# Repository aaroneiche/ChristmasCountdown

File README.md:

# Christmas Countdown

Christmas Countdown is a Christmas Ornament that counts down to Christmas day (or really any day) in Binary. Using two rows of LEDs, it displays the Days & Hours and then the Minutes & seconds remaining until Christmas Day. If you want to learn about how I approached developing it, and how many times I got it wrong, you can read my writeup of [the whole adventure here](https://aaroneiche.com/2023/02/05/christmas-countdown/) 

The heart of the circuit is an ESP32-C3-Mini-1. It drives fourteen SK6812 LEDs that display the time, as well as an indicator of the current mode. The time is kept by a PCF85363 with a battery backup . The ornament runs off of 5v, and requires about 1A with the LEDs running at full brightness (I do not recommend this, these LEDs will melt your face off) 

### Setting the time.

To set the ornament, press and hold the left button for 3 seconds and release. On the bottom row it shows what you're setting (year, month, day, hour, minute, second) and the top row displays the current value. There are 12 settings in all, 6 for the current date/time, and 6 for the target date/time. You can advance to the next value to set by pressing the left button. You can increase the value by pressing the right button. The value will return to zero (or one) after the maximum value has been reached. You do not need to do any math about timing, just set the current and target dates/times. The default target date is December 25th, 00:00:00 AM. You may wish to set the time to December 25th, 08:00:00 for when you start Christmas with your family. Perhaps you observe Orthodox Christmas and want to set it for January 7th.

When setting the current date/time, the whole bottom row will be lit with the value you're setting flashing on and off.
Here is an example of setting the current year (22 - for 2022)

When setting the target date/time, the whole bottom row will be off with the value you're setting flashing on an off.
Here is an example of setting the target month (12 - for December)

When you've finished setting the values, press and hold the right button for 3 seconds. The countdown values will appear.

## Clock battery

If power is lost to Christmas Countdown, the RTC will go into battery mode automatically and will continue to count time. The RTC battery runs on very low power mode consuming ~320nA. 

If the battery is removed, some settings will be maintained on Christmas Countdown. The current time will need to be set again.

## Adding to the the software

I wrote most of this software in VSCode with PlatformIO. I programmed the Esp32-C3 using a CP1202 USB->UART adapter, and connecting the DTR and RTS pins. Alternatively, you should be able to put the board in download mode by holding down the "Program" button on the back while pressing and releasing the "Reset" button.

Changes to the firmware should be pretty easy to make. It's all (in)conveniently in a single file. A couple of helpful hints: 

A clock interrupt fires 1024 times a second. This is how the clock, and the various display updates are handled. There are currently events that execute at 1s, 0.5s and 0.25s. Any handler can be added to the `quarterSecondOverflow`, `halfSecondOverflow`, and `secondOverflow` branches in the loop. These are good locations for executing frequent.

The very last execution in the loop is to update the display. This creates a buffer and that is fed to the `displayFromBuffer` method. This should make it easy to set the display to whatever you want. To prevent your LEDs from getting overwritten by other stuff, make sure to pay attention to the other modes that are writing to the display. The easiest way to avoid this is to make your own Display Mode - you can add one about line 50 in the `enum DisplayMode`.

# Hardware

I typically order PCBs with 1oz copper, HASL Lead-Free. The Color isn't super important. I think that Black looks best, and if you're willing to splurge, Gold ENIG looks very nice on the Snowflake on the front.

The Piezo buzzer does not currently do anything. I have run some tests where I can get it to play some simple music. It definitely works, I just haven't done anything with it yet.

Taking advantage of the Interact HTML BOM, there's a component placement page included in this repo (`ibom.html`)

## What about Wifi?!?!

Yes, the onboard chip has support for Wifi. Which means that you could set the time automatically using NTP. And you could change settings on a webpage even! I have written some code to support these features, and when they're polished I will be making them available. For now, Christmas countdown must be programmed using a couple of buttons and your cunning.

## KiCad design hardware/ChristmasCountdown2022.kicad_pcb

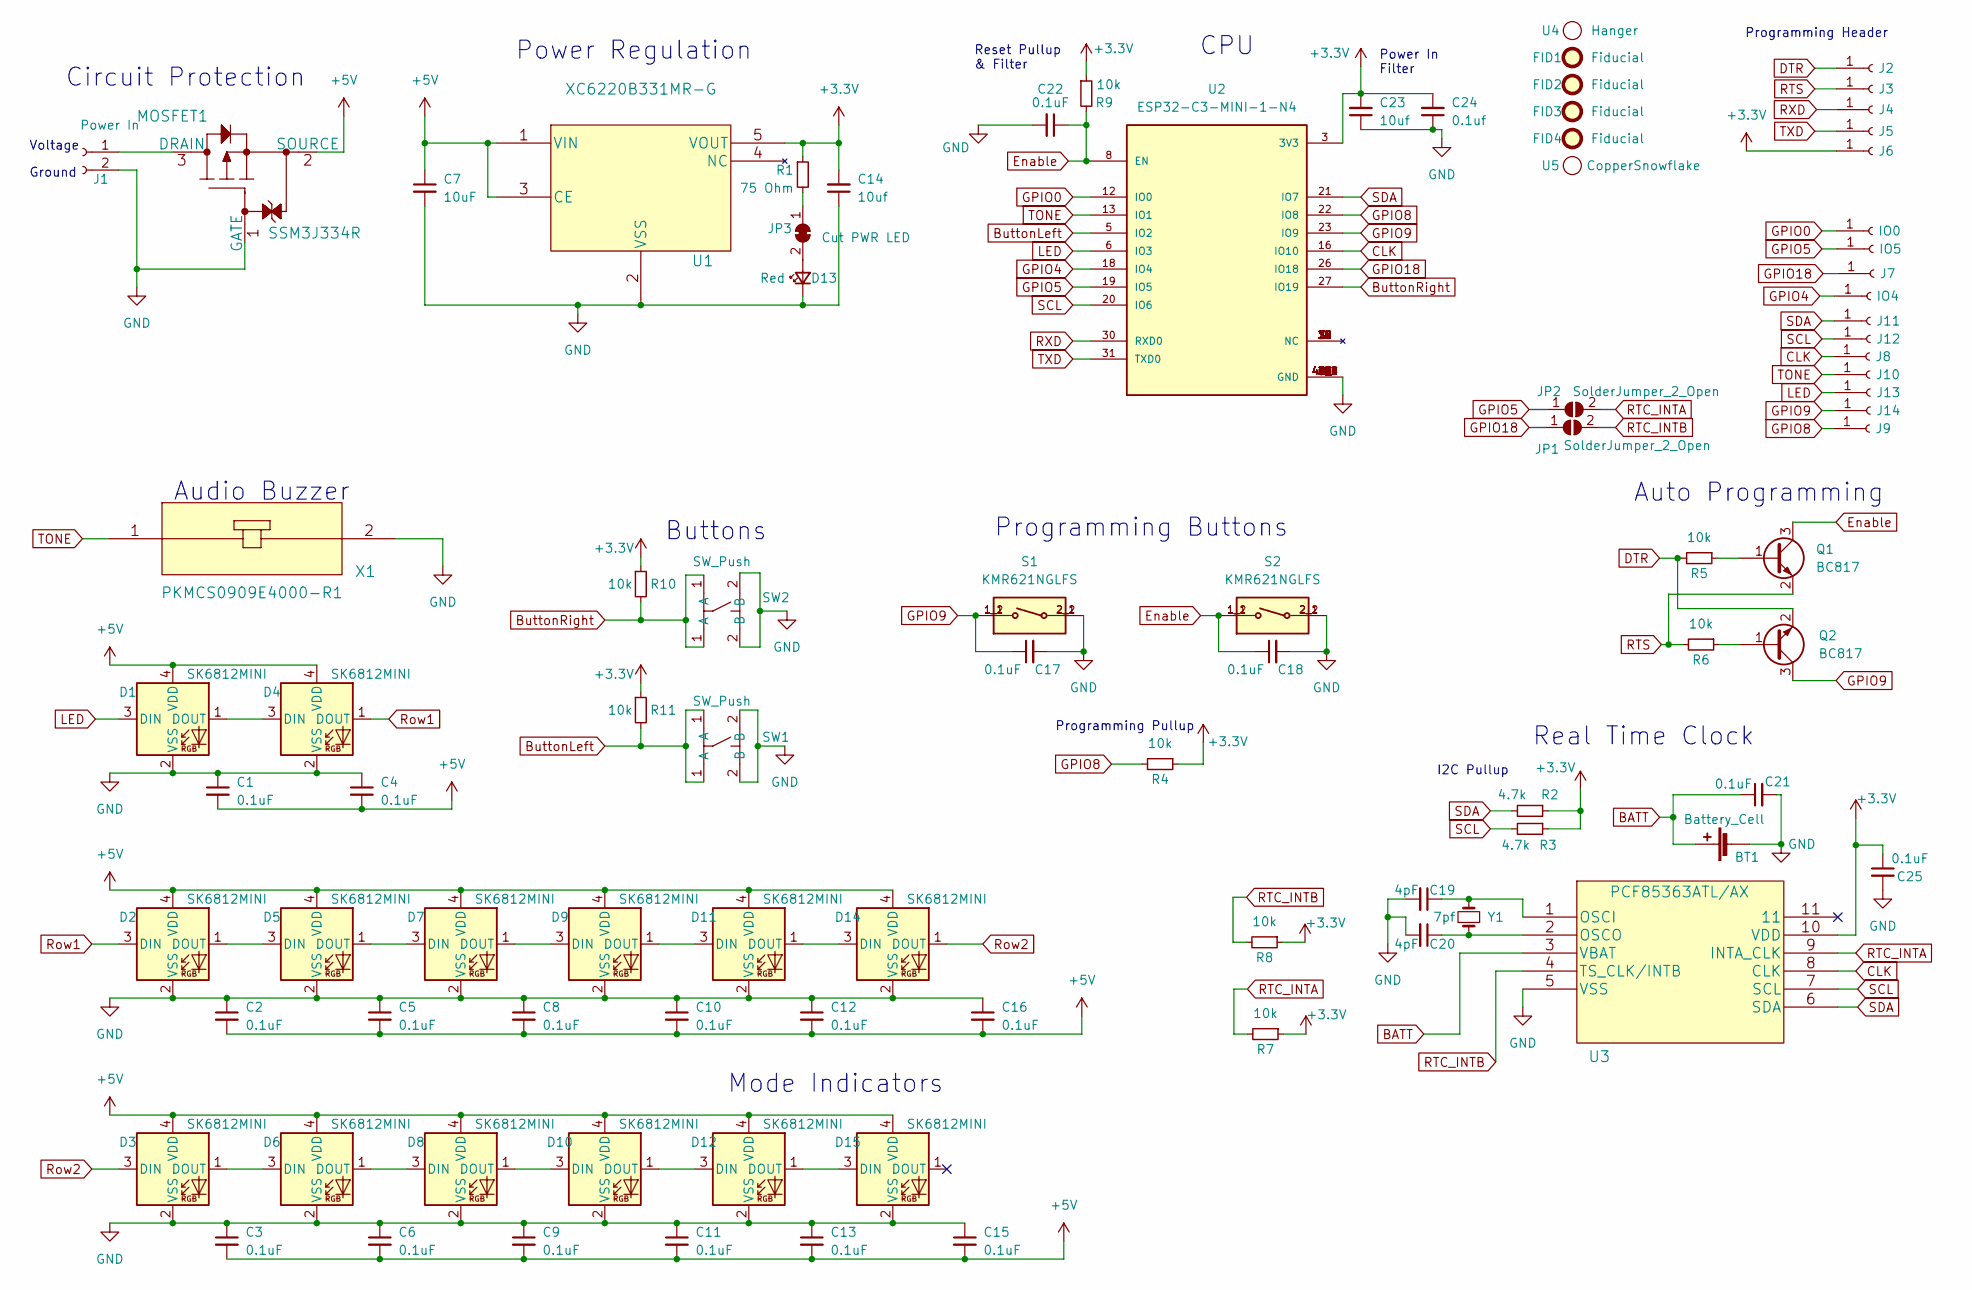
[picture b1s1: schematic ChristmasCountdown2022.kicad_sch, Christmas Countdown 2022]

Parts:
BT1: Battery_Cell; BatteryHolder_LINX_BAT-HLD-012-SMT
C1, C2, C3, C4, C5, C6, C8, C9, C10, C11, C12, C13, C15, C16, C17, C18, C21, C22, C25: 0.1uF; C_0805_2012Metric
C7: 10uF; C_0805_2012Metric
C14, C23: 10uf; C_0805_2012Metric
C19, C20: 4pF; R_0805_2012Metric
C24: 0.1uf; C_0805_2012Metric
D1, D2, D3, D4, D5, D6, D7, D8, D9, D10, D11, D12, D14, D15: SK6812MINI; LED_SK6812MINI_PLCC4_3.5x3.5mm_P1.75mm
D13: Red; LED_0805_2012Metric
FID1, FID2, FID3, FID4: Fiducial; Fiducial_0.5mm_Mask1mm
IO0: IO0; TestPoint_Pad_D2.0mm
IO4: IO4; TestPoint_Pad_D2.0mm
IO5: IO5; TestPoint_Pad_D2.0mm
J1: Power In; Hand_solderable_1x2
J2, J3, J4, J5, J6: Conn_01x01_Female; PinSocket_1x01_P2.54mm_Vertical
J7: IO18; TestPoint_Pad_D2.0mm
J8: CLK; PinSocket_1x01_P2.54mm_Vertical
J9: IO8; TestPoint_Pad_D2.0mm
J10: TONE; PinSocket_1x01_P2.54mm_Vertical
J11: SDA; TestPoint_Pad_D2.0mm
J12: SCL; TestPoint_Pad_D2.0mm
J13: LED; PinSocket_1x01_P2.54mm_Vertical
J14: IO9; TestPoint_Pad_D2.0mm
JP1, JP2: SolderJumper_2_Open; SolderJumper-2_P1.3mm_Open_RoundedPad1.0x1.5mm
JP3: Cut PWR LED; SolderJumper-2_P1.3mm_Bridged_RoundedPad1.0x1.5mm
MOSFET1: SSM3J334R
Q1, Q2: BC817; SOT-23
R1: 75 Ohm; R_0805_2012Metric
R2, R3: 4.7k; R_0805_2012Metric
R4, R5, R6, R7, R8, R9, R10, R11: 10k; R_0805_2012Metric
S1, S2: KMR621NGLFS; SW_KMR621NGLFS; PARTREV N/A
SW1, SW2: SW_Push; EVQQ2B03W; MFG_Part_number EVQ-Q2F02W
U1: XC6220B331MR-G
U2: ESP32-C3-MINI-1-N4; XCVR_ESP32-C3-MINI-1-N4; PARTREV v1.0
U3: PCF85363ATL/AX; PCF85363ATL_AX
U4: Hanger
U5: CopperSnowflake; CopperSnowflakeGraphic
X1: PKMCS0909E4000-R1
Y1: 7pf; CM8V-T1A-Crystal

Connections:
+3.3V: C14.2, C23.2, C24.2, C25.1, J6.1, R1.1, R2.1, R3.1, R4.1, R7.1, R8.1, R9.1, R10.1, R11.1, U1.5 (VOUT), U2.3 (3V3), U3.10 (VDD)
+5V: C1.2, C2.2, C3.2, C4.2, C5.2, C6.2, C7.1, C8.2, C9.2, C10.2, C11.2, C12.2, C13.2, C15.2, C16.2, D1.4 (VDD), D2.4 (VDD), D3.4 (VDD), D4.4 (VDD), D5.4 (VDD), D6.4 (VDD), D7.4 (VDD), D8.4 (VDD), D9.4 (VDD), D10.4 (VDD), D11.4 (VDD), D12.4 (VDD), D14.4 (VDD), D15.4 (VDD), MOSFET1.2 (SOURCE), U1.1 (VIN), U1.3 (CE)
BATT: BT1.1 (+), C21.1, U3.3 (VBAT)
ButtonLeft: R11.2, SW1.1 (A), U2.5 (IO2)
ButtonRight: R10.2, SW2.1 (A), U2.27 (IO19)
CLK: J8.1, U2.16 (IO10), U3.8 (CLK)
DTR: J2.1, Q2.2 (E), R5.2
Enable: C18.1, C22.1, Q1.3 (C), R9.2, S2.1_1, S2.1_2, U2.8 (EN)
GND: BT1.2 (-), C1.1, C2.1, C3.1, C4.1, C5.1, C6.1, C7.2, C8.1, C9.1, C10.1, C11.1, C12.1, C13.1, C14.1, C15.1, C16.1, C17.2, C18.2, C19.2, C20.2, C21.2, C22.2, C23.1, C24.1, C25.2, D1.2 (VSS), D2.2 (VSS), D3.2 (VSS), D4.2 (VSS), D5.2 (VSS), D6.2 (VSS), D7.2 (VSS), D8.2 (VSS), D9.2 (VSS), D10.2 (VSS), D11.2 (VSS), D12.2 (VSS), D13.1 (K), D14.2 (VSS), D15.2 (VSS), J1.2, MOSFET1.1 (GATE), S1.2_1, S1.2_2, S2.2_1, S2.2_2, SW1.2 (B), SW2.2 (B), U1.2 (VSS), U2.1 (GND), U2.2 (GND), U2.11 (GND), U2.14 (GND), U2.36 (GND), U2.37 (GND), U2.38 (GND), U2.39 (GND), U2.40 (GND), U2.41 (GND), U2.42 (GND), U2.43 (GND), U2.44 (GND), U2.45 (GND), U2.46 (GND), U2.47 (GND), U2.48 (GND), U2.49_1 (GND), U2.49_2 (GND), U2.49_3 (GND), U2.49_4 (GND), U2.49_5 (GND), U2.49_6 (GND), U2.49_7 (GND), U2.49_8 (GND), U2.49_9 (GND), U2.50 (GND), U2.51 (GND), U2.52 (GND), U2.53 (GND), U3.5 (VSS), X1.2
GPIO0: IO0.1, U2.12 (IO0)
GPIO4: IO4.1, U2.18 (IO4)
GPIO5: IO5.1, JP2.1 (A), U2.19 (IO5)
GPIO8: J9.1, R4.2, U2.22 (IO8)
GPIO9: C17.1, J14.1, Q2.3 (C), S1.1_1, S1.1_2, U2.23 (IO9)
GPIO18: J7.1, JP1.1 (A), U2.26 (IO18)
LED: D1.3 (DIN), J13.1, U2.6 (IO3)
unnamed: C19.1, U3.1 (OSCI), Y1.2
unnamed: C20.1, U3.2 (OSCO), Y1.1
unnamed: D1.1 (DOUT), D4.3 (DIN)
unnamed: D2.1 (DOUT), D5.3 (DIN)
unnamed: D3.1 (DOUT), D6.3 (DIN)
unnamed: D5.1 (DOUT), D7.3 (DIN)
unnamed: D6.1 (DOUT), D8.3 (DIN)
unnamed: D7.1 (DOUT), D9.3 (DIN)
unnamed: D10.1 (DOUT), D12.3 (DIN)
unnamed: D8.1 (DOUT), D10.3 (DIN)
unnamed: D11.1 (DOUT), D14.3 (DIN)
unnamed: D9.1 (DOUT), D11.3 (DIN)
unnamed: D12.1 (DOUT), D15.3 (DIN)
unnamed: D13.2 (A), JP3.2 (B)
unnamed: J1.1, MOSFET1.3 (DRAIN)
unnamed: JP3.1 (A), R1.2
unnamed: Q1.1 (B), R5.1
unnamed: Q2.1 (B), R6.1
RTC_INTA: JP2.2 (B), R7.2, U3.9 (INTA_CLK)
RTC_INTB: JP1.2 (B), R8.2, U3.4 (TS_CLK/INTB)
RTS: J3.1, Q1.2 (E), R6.2
RXD: J4.1, U2.30 (RXD0)
Row1: D2.3 (DIN), D4.1 (DOUT)
Row2: D3.3 (DIN), D14.1 (DOUT)
SCL: J12.1, R3.2, U2.20 (IO6), U3.7 (SCL)
SDA: J11.1, R2.2, U2.21 (IO7), U3.6 (SDA)
TONE: J10.1, U2.13 (IO1), X1.1
TXD: J5.1, U2.31 (TXD0)

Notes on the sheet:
Auto Programming
Circuit Protection
Power Regulation
CPU
Programming Header
Real Time Clock
Programming Pullup
Mode Indicators
Audio Buzzer
I2C Pullup
Buttons
Voltage
Power In Filter
Ground
Programming Buttons
Reset Pullup & Filter

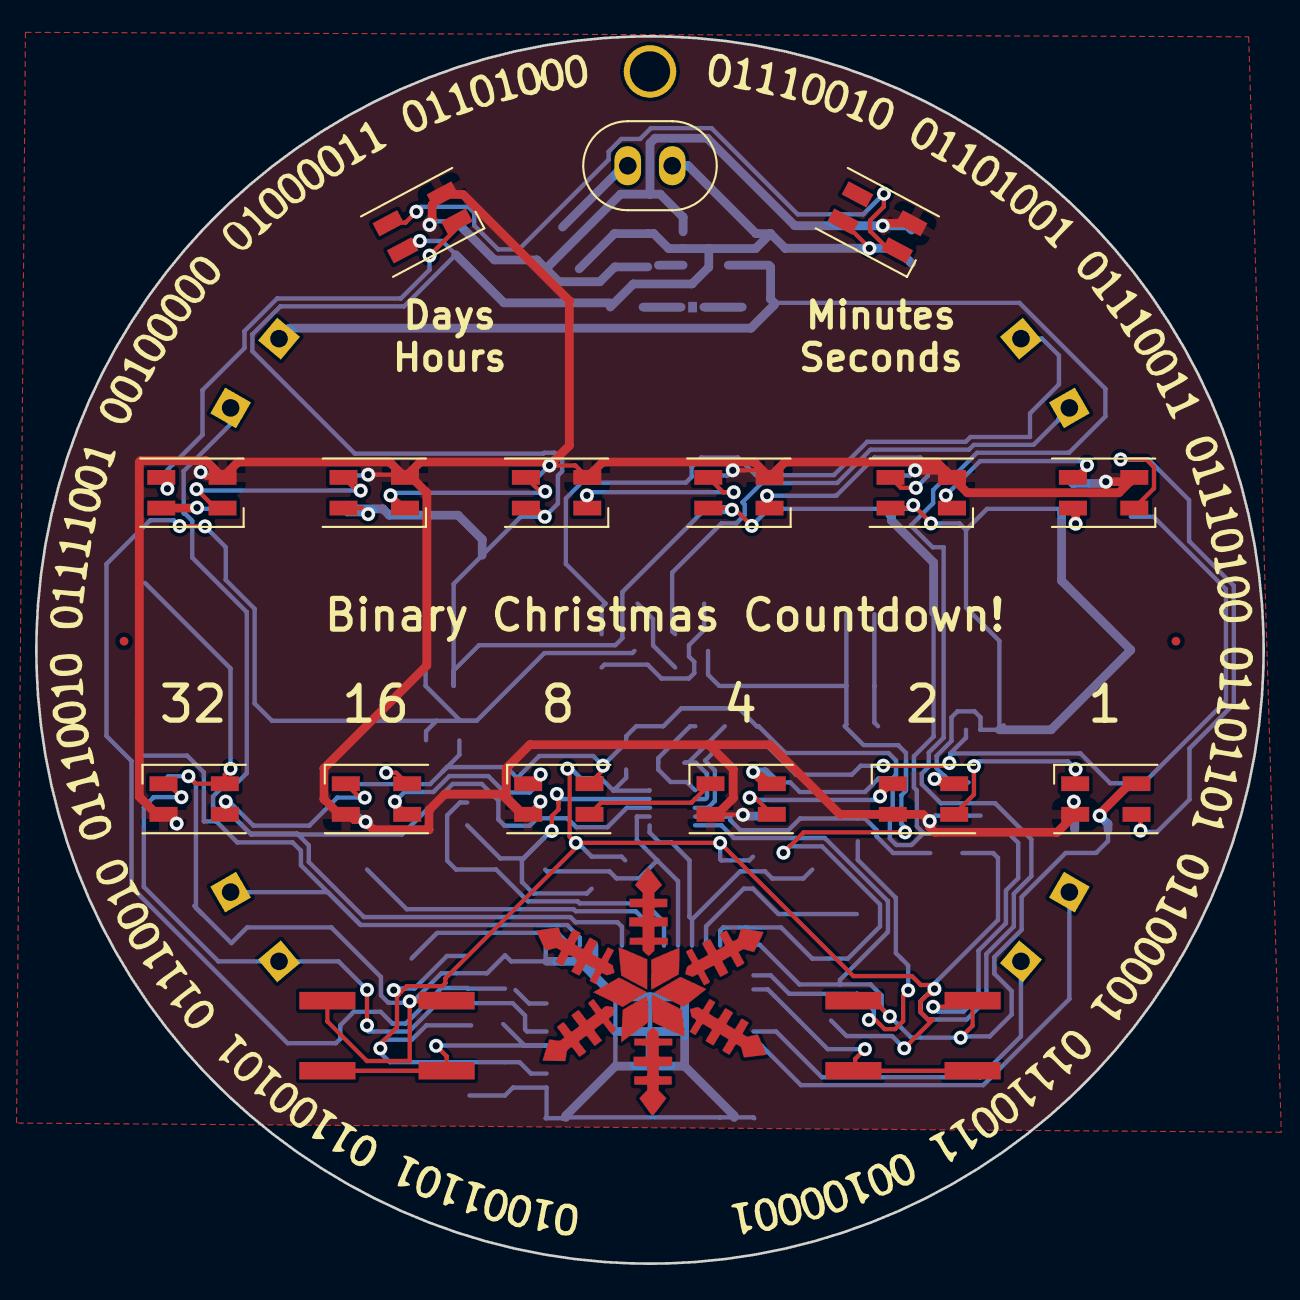
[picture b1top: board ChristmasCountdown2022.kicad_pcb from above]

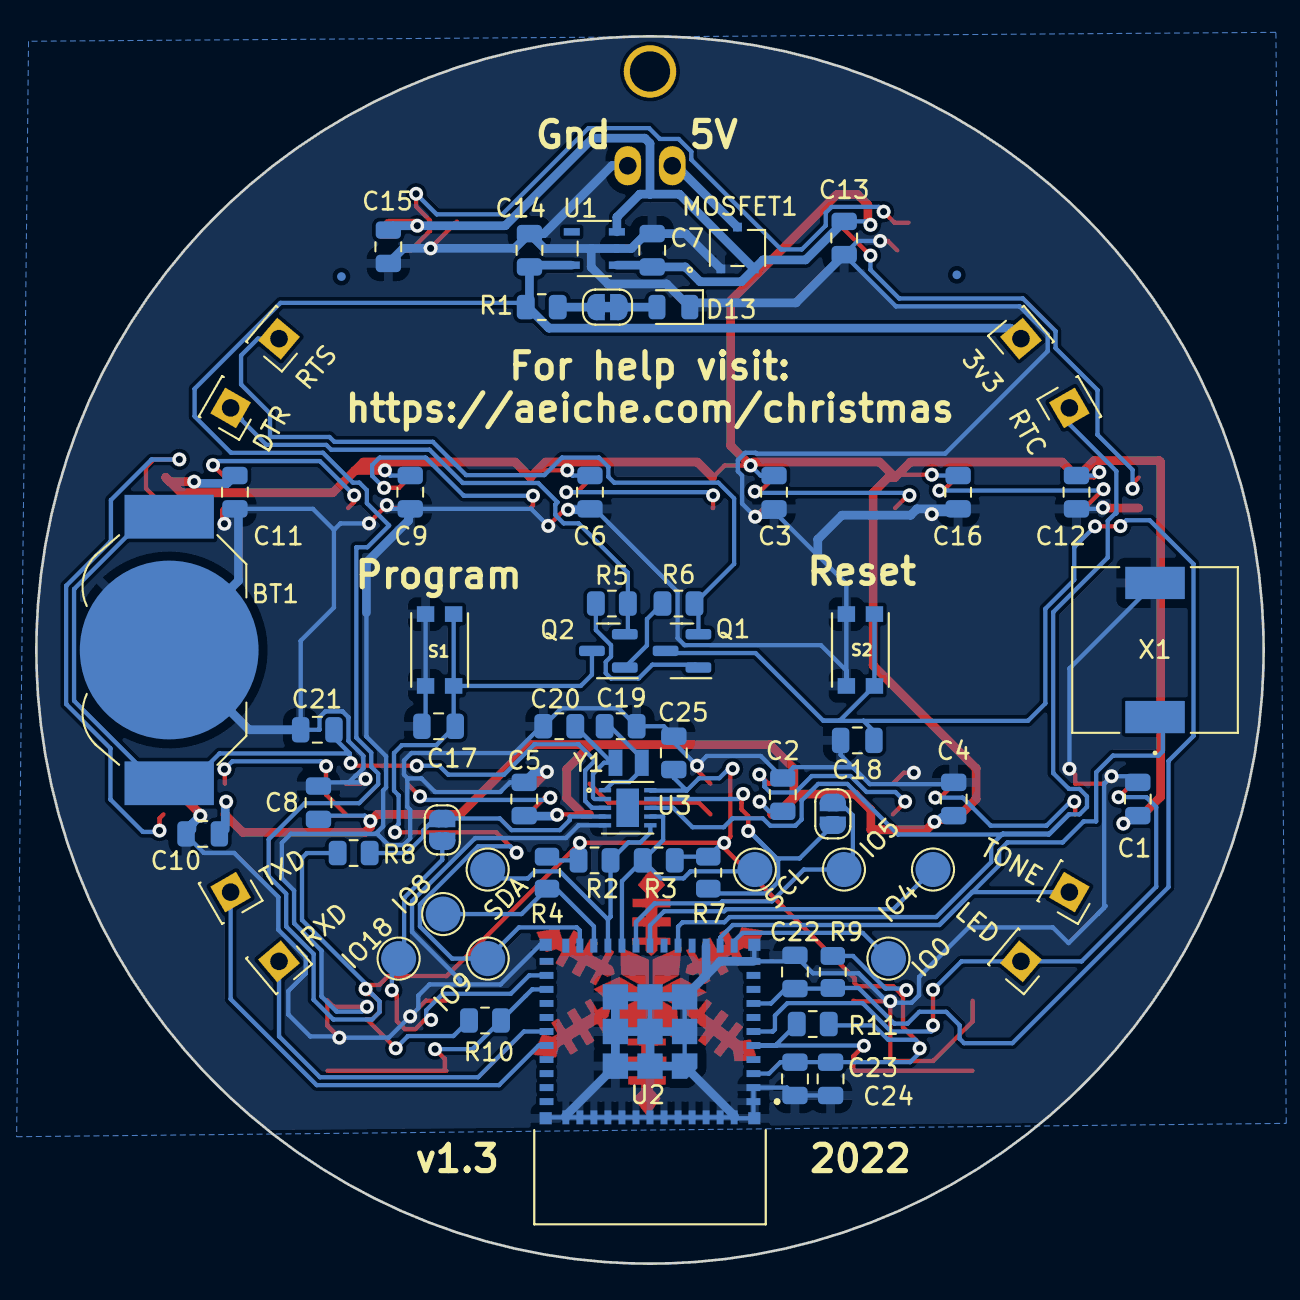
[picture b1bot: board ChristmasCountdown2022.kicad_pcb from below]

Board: 2 copper layers, 70.0 x 70.0 mm, 90 parts (69 on the bottom side), 44 nets.

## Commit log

2023-02-06 Initial commit - Readme, Code, Images.
2023-02-06 Footprints, board files, schematic, etc.
2023-02-06 Adds clarification about Wifi to Readme
2023-02-08 Adds License file

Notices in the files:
parts and their libraries:
Copyright 2021 Accelerated Designs. All rights reserved.
